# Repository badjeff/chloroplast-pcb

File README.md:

# chloroplast

A nRF52840 controller with the [Ebyte E73-2G4M08S1C module](https://www.cdebyte.com/products/E73-2G4M08S1C), [TI BQ25186DLHR](https://www.ti.com/product/BQ25186/part-details/BQ25186DLHR), and [TI TPS7A0233PDBVR](https://www.ti.com/product/TPS7A02/part-details/TPS7A0233PDBVR).

## PCB

Online preview avaliable [here](https://kicanvas.org/?github=https%3A%2F%2Fgithub.com%2Fbadjeff%2Fchloroplast-pcb), powered by [KiCanvas](https://github.com/theacodes/kicanvas).

<p float="left">

</P>

*Figure 1: PCB edgecuts dimension*

*Figure 2: PCB 3D View - 1.0mm FR4*

*Figure 3: Schematic*

### BOM

|Designator|Footprint|Quantity|Value|LCSC Part #|
|-|-|-|-|-|
|C1,C2,C3,C4|0402|4|1uF|C52923|
|C5,C6|0402|2|10uF|C15525|
|D1|0402|1|GREEN LED|C20608784|
|D2|0402|1|BLUE LED|C434447|
|D3,D4|0402|2|NSR05F30NXT5G|C604339|
|L1|0603|1|10uH|C76798|
|R1,R2|0402|2|5K1|C25905|
|R3,R4,R5,R9|0402|4|10K|C25744|
|R6|0402|1|510K|C11616|
|R7|0402|1|4K7|C25900|
|R8|0402|1|1M|C2909328|
|R10|0402|1|820K|C2909386|
|R11|0402|1|2M|C2930015|
|U1|E73-2G4M08S1C|1|E73-2G4M08S1C|C356849|
|U2|DFN-10_2x2mm_P0.4mm|1|BQ25186DLHR|C44639442|
|U3|SOT-23-5|1|TPS7A0233PDBVR|C2887324|
|U4|WLCSP-4L|1|TPMAX40200ANS_T|C47117620|
|USBC1|USB_C_Receptacle|1|TYPE-C-31-M-12|C165948|

- SMD 0402 (Imperial) aka 1005 Metric.
- Alternative LED pads (D5,D6) are layouted on back.

### Board Characteristics

- Copper layer count: 2
- Board thickness: 1.0 mm
- Board overall dimensions: 18.0 x 33.02 mm

### Bootloader

This board uses Adafruit Bootloader. The board folder could be found at [here](https://github.com/adafruit/Adafruit_nRF52_Bootloader/compare/master...badjeff:Adafruit_nRF52_Bootloader:master). Bootloader flashing is recommended to follow the comprehensive guide on [joric/nrfmicro/wiki/Bootloader](https://github.com/joric/nrfmicro/wiki/Bootloader).

### Zephye/ZMK Board Config

Zephyr and ZMK board config could be found in [chloroplast-zmk-module](https://github.com/badjeff/chloroplast-zmk-module). ZMK sheild example could be found in [shields/chlorotaro34](https://github.com/badjeff/zmk-config/tree/a3d11110aed00859894f039f29c2347270b4b8b8/boards/shields/chlorotaro34).

## License

Available under the [CERN-OHL-P v2](/LICENSE) permissive license.

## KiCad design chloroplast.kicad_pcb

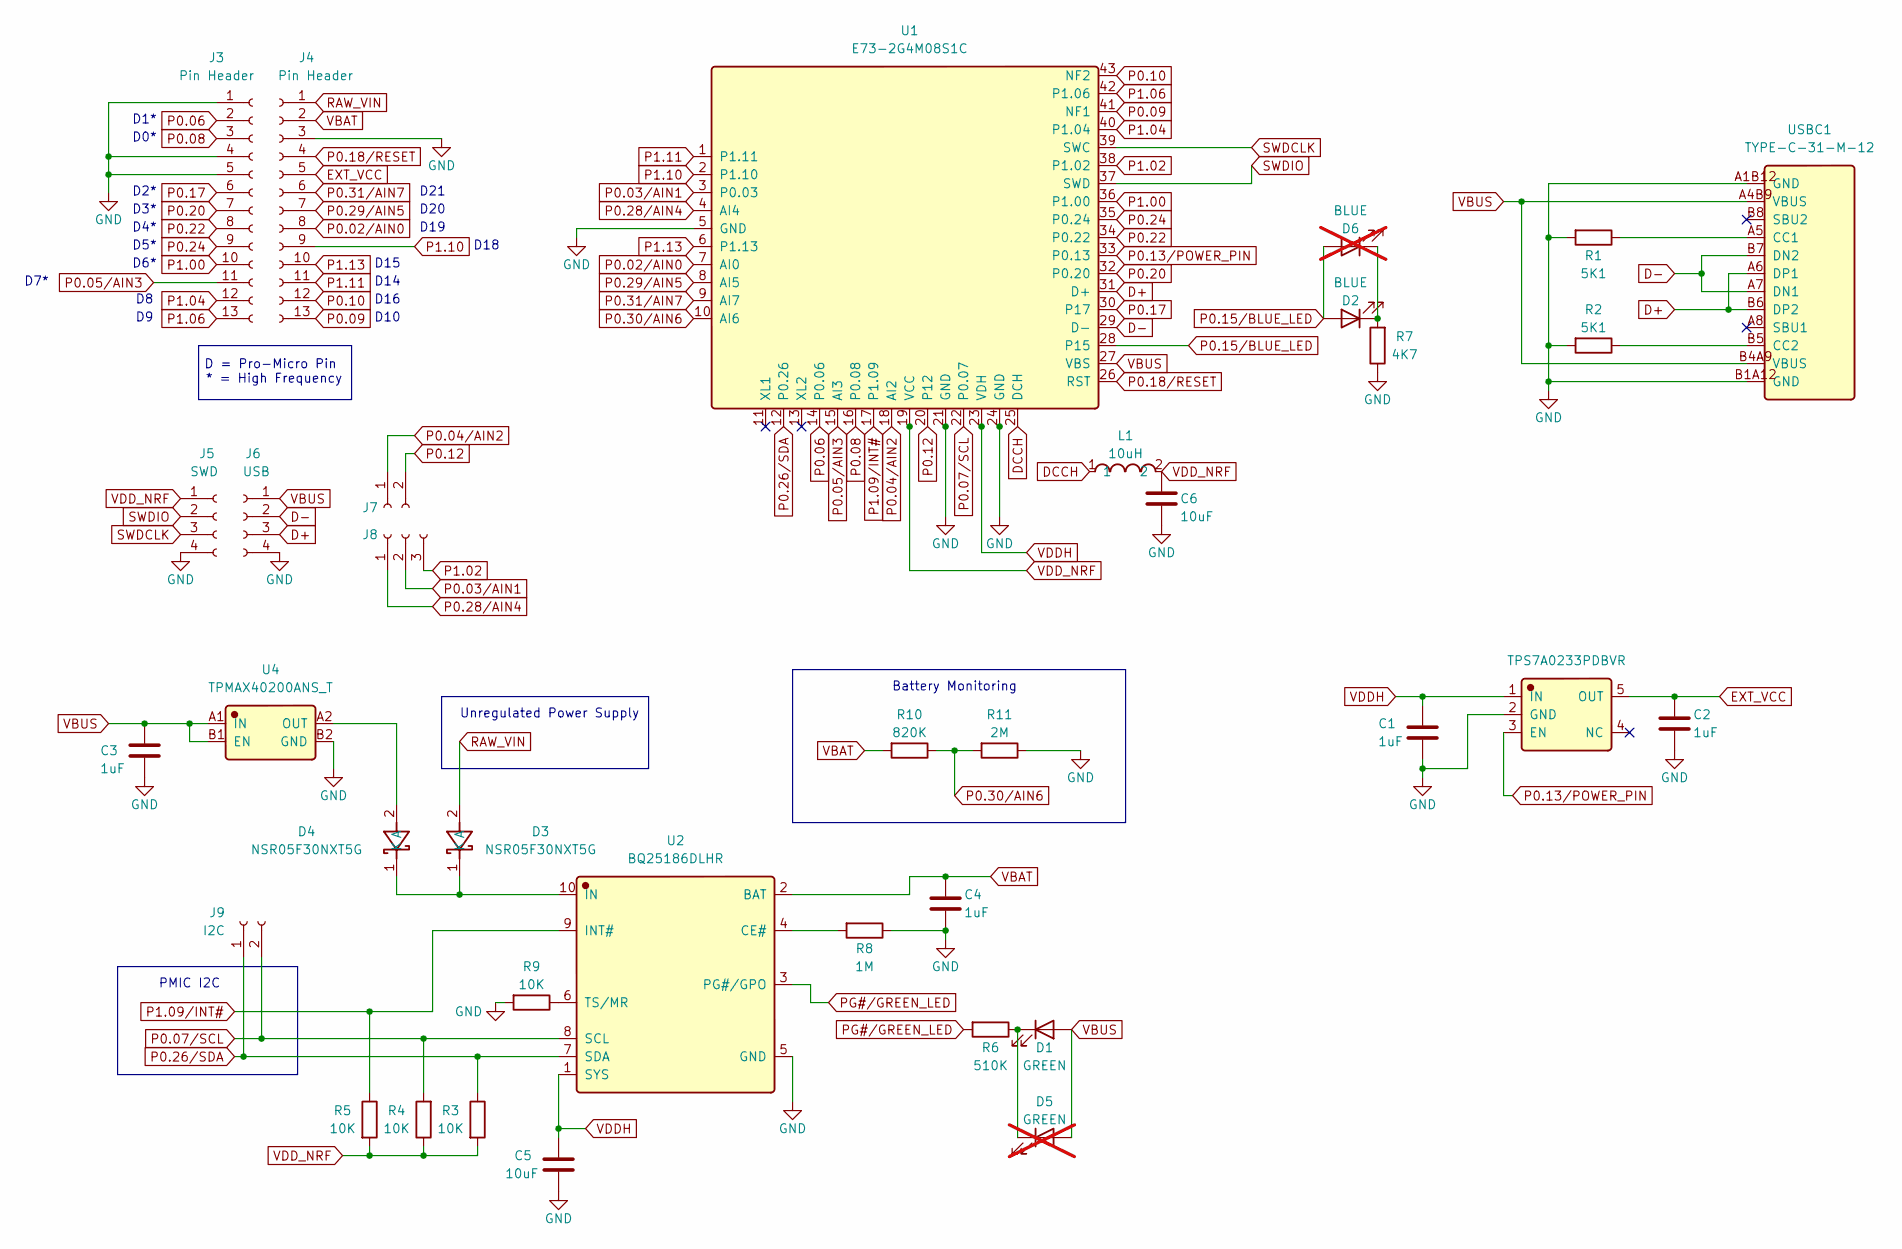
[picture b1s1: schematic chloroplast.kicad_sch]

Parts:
C1, C2, C3, C4: 1uF; C_0402_1005Metric; LCSC C52923
C5, C6: 10uF; C_0402_1005Metric; LCSC C15525
D1: GREEN; LED_0402_1005Metric; LCSC C20608784
D2: BLUE; LED_0402_1005Metric; LCSC C434447
D3, D4: NSR05F30NXT5G; Manufacturer Part NSR05F30NXT5G; LCSC C604339
D5: GREEN; LED_0402_1005Metric; LCSC C20608784; not fitted
D6: BLUE; LED_0402_1005Metric; LCSC C434447; not fitted
J3, J4: Pin Header; PinHeader_1x13_P2.54mm_Vertical
J5: SWD; PinHeader_1x04_P1.27mm_Vertical
J6: USB; PinHeader_1x04_P1.27mm_Vertical
J7: Conn_01x02_Socket; PinHeader_1x02_P1.27mm_Vertical
J8: Conn_01x04_Socket; PinHeader_1x03_P1.27mm_Vertical
J9: I2C; PinHeader_1x02_P1.27mm_Vertical
L1: 10uH; L_0603_1608Metric; Manufacturer Part MLZ1608M100WT000; LCSC C76798
R1, R2: 5K1; R_0402_1005Metric; LCSC C25905
R3, R4, R5, R9: 10K; R_0402_1005Metric; LCSC C25744
R6: 510K; R_0402_1005Metric; LCSC C11616
R7: 4K7; R_0402_1005Metric; LCSC C25900
R8: 1M; R_0402_1005Metric; LCSC C2909328
R10: 820K; R_0402_1005Metric; LCSC C2909386
R11: 2M; R_0402_1005Metric; LCSC C2930015
U1: E73-2G4M08S1C; Manufacturer Part E73-2G4M08S1C; LCSC C356849
U2: BQ25186DLHR; DFN-10_2x2mm_P0.4mm; Manufacturer Part BQ25186DLHR; LCSC C44639442
U3: TPS7A0233PDBVR; SOT-23-5; Manufacturer Part TPS7A0233PDBVR; LCSC C2887324
U4: TPMAX40200ANS_T; WLCSP-4_0.64x0.64mm_P0.35mm; Manufacturer Part TPMAX40200ANS+T; LCSC C47117620
USBC1: TYPE-C-31-M-12; USB_C_Receptacle_HRO_TYPE-C-31-M-12; Manufacturer Part TYPE-C-31-M-12; LCSC C165948

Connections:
D+: J6.3, U1.31 (D+), USBC1.A6 (DP1), USBC1.B6 (DP2)
D-: J6.2, U1.29 (D-), USBC1.A7 (DN1), USBC1.B7 (DN2)
DCCH: L1.1, U1.25 (DCH)
EXT_VCC: C2.1, J4.5, U3.5 (OUT)
GND: C1.2, C2.2, C3.2, C4.2, C5.2, C6.2, J3.1, J3.4, J3.5, J4.3, J5.4, J6.4, R1.2, R2.2, R7.1, R8.1, R9.2, R11.1, U1.5 (GND), U1.21 (GND), U1.24 (GND), U2.5 (GND), U3.2 (GND), U4.B2 (GND), USBC1.A1B12 (GND), USBC1.B1A12 (GND)
unnamed: D1.1 (K), D5.1 (K), R6.1
unnamed: D2.1 (K), D6.1 (K), R7.2
unnamed: D3.1 (K), D4.1 (K), U2.10 (IN)
unnamed: D4.2 (A), U4.A2 (OUT)
unnamed: R8.2, U2.4 (CE#)
unnamed: R9.1, U2.6 (TS/MR)
unnamed: R1.1, USBC1.A5 (CC1)
unnamed: R2.1, USBC1.B5 (CC2)
P0.02/AIN0: J4.8, U1.7 (AI0)
P0.03/AIN1: J8.2, U1.3 (P0.03)
P0.04/AIN2: J7.1, U1.18 (AI2)
P0.05/AIN3: J3.11, U1.15 (AI3)
P0.06: J3.2, U1.14 (P0.06)
P0.07/SCL: J9.2, R4.2, U1.22 (P0.07), U2.8 (SCL)
P0.08: J3.3, U1.16 (P0.08)
P0.09: J4.13, U1.41 (NF1)
P0.10: J4.12, U1.43 (NF2)
P0.12: J7.2, U1.20 (P12)
P0.13/POWER_PIN: U1.33 (P0.13), U3.3 (EN)
P0.15/BLUE_LED: D2.2 (A), D6.2 (A), U1.28 (P15)
P0.17: J3.6, U1.30 (P17)
P0.18/RESET: J4.4, U1.26 (RST)
P0.20: J3.7, U1.32 (P0.20)
P0.22: J3.8, U1.34 (P0.22)
P0.24: J3.9, U1.35 (P0.24)
P0.26/SDA: J9.1, R3.1, U1.12 (P0.26), U2.7 (SDA)
P0.28/AIN4: J8.1, U1.4 (AI4)
P0.29/AIN5: J4.7, U1.8 (AI5)
P0.30/AIN6: R10.1, R11.2, U1.10 (AI6)
P0.31/AIN7: J4.6, U1.9 (AI7)
P1.00: J3.10, U1.36 (P1.00)
P1.02: J8.3, U1.38 (P1.02)
P1.04: J3.12, U1.40 (P1.04)
P1.06: J3.13, U1.42 (P1.06)
P1.09/INT#: R5.1, U1.17 (P1.09), U2.9 (INT#)
P1.10: J4.9, U1.2 (P1.10)
P1.11: J4.11, U1.1 (P1.11)
P1.13: J4.10, U1.6 (P1.13)
PG#/GREEN_LED: R6.2, U2.3 (PG#/GPO)
RAW_VIN: D3.2 (A), J4.1
SWDCLK: J5.3, U1.39 (SWC)
SWDIO: J5.2, U1.37 (SWD)
VBAT: C4.1, J4.2, R10.2, U2.2 (BAT)
VBUS: C3.1, D1.2 (A), D5.2 (A), J6.1, U1.27 (VBS), U4.A1 (IN), U4.B1 (EN), USBC1.A4B9 (VBUS), USBC1.B4A9 (VBUS)
VDDH: C1.1, C5.1, U1.23 (VDH), U2.1 (SYS), U3.1 (IN)
VDD_NRF: C6.1, J5.1, L1.2, R3.2, R4.1, R5.2, U1.19 (VCC)

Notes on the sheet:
Unregulated Power Supply
D20
D19
D18
Battery Monitoring
D21
D14
D6*
D15
D5*
D3*
D16
D1*
D = Pro-Micro Pin * = High Frequency
D4*
D0*
D2*
D10
PMIC I2C
D7*

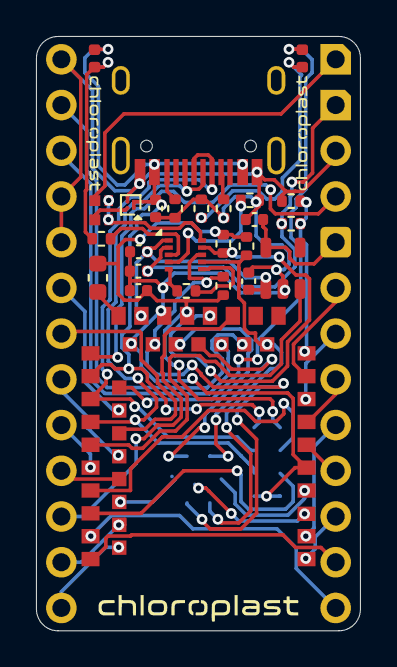
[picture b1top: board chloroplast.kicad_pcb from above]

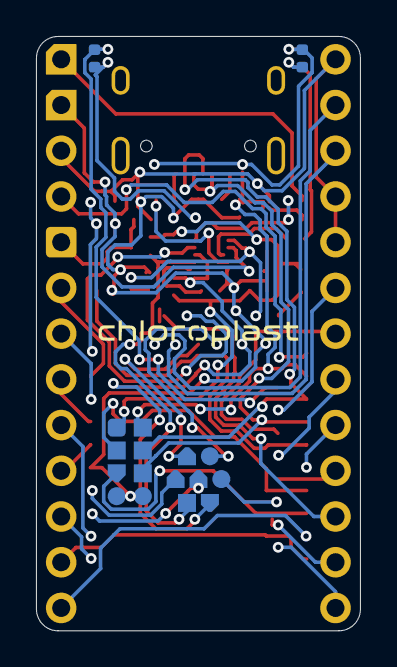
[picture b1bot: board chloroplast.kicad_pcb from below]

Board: 2 copper layers, 18.0 x 33.0 mm, 36 parts (7 on the bottom side), 51 nets.

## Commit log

2026-06-03 init
2026-06-03 add hyperlinks in readme
2026-06-04 add pro-micro pin numbers in schematic
2026-06-10 change L1 to TDK MLZ1608M100WT000
